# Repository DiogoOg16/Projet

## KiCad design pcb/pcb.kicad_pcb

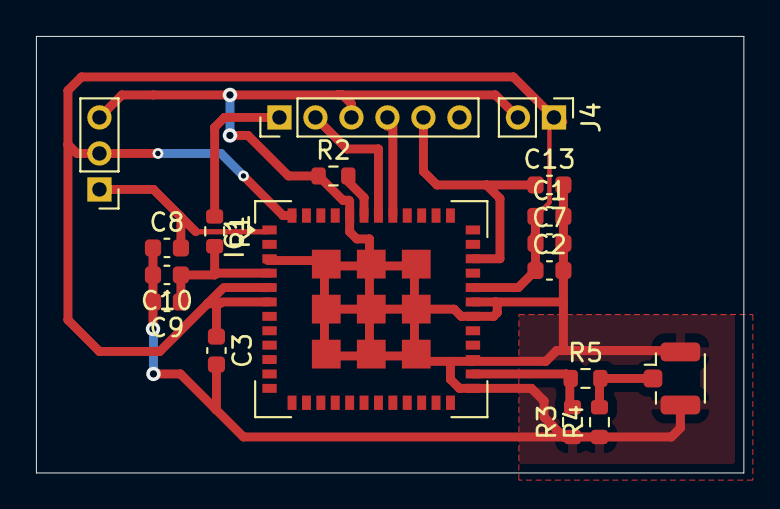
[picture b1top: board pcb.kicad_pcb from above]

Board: 2 copper layers, 39.3 x 24.2 mm, 18 parts (0 on the bottom side), 11 nets.

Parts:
C1, C9: 10uf; C_0603_1608Metric
C2, C13: 1uf; C_0603_1608Metric
C3, C7, C10: 0.1uf; C_0603_1608Metric
C8: 100pf; C_0603_1608Metric
IC1: CMWX1ZZABZ-093; CMWX1ZZABZ
J1: U.FL-R-SMT_01_; U.FL_Hirose_U.FL-R-SMT-1_Vertical
J2: Conn_01x06; PinHeader_1x06_P2.00mm_Vertical
J3: Conn_01x03_Pin; PinHeader_1x03_P2.00mm_Vertical
J4: Conn_01x02_Pin; PinHeader_1x02_P2.00mm_Vertical
R1, R5: 0R; R_0603_1608Metric
R2: 1M; R_0603_1608Metric
R3, R4: DNP; R_0603_1608Metric

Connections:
/debimetre: C8.2, IC1.1 (PA12/USB_DP_), J3.1
/rst: C13.1, IC1.34 (MCU_NRST), J2.5
/swclk: IC1.42 (PA14/SWCLK), J2.2
/swdio: IC1.41 (PA13/SWDIO), J2.4
/vdd: C1.1, C2.1, C3.1, C7.1, IC1.5 (VDD_MCU), IC1.6 (VDD_RF), IC1.32 (VREF+), IC1.48 (VDD__TCXO), J3.2, J4.1
/vdd_usb: C9.1, C10.1, IC1.4 (VDD_USB), R1.2
Earth: C1.2, C2.2, C3.2, C7.2, C8.1, C9.2, C10.2, C13.2, IC1.3 (GND_1), IC1.25 (GND_3), IC1.27 (GND_4), IC1.30 (DBG_CRF2), IC1.31 (STSAFE_NRST), IC1.44 (GND_5), IC1.49 (GND_6), IC1.50 (GND_7), IC1.51 (GND_8), IC1.52 (GND_9), IC1.53 (GND_10), IC1.54 (GND_11), IC1.55 (GND_12), IC1.56 (GND_13), IC1.57 (GND_14), J1.2 (GND), J2.3, J3.3, J4.2, R2.1, R3.1, R4.1
unnamed: IC1.26 (ANT), R3.2, R5.1
unnamed: IC1.43 (BOOT0), R2.2
unnamed: J1.1 (GND), R4.2, R5.2
unnamed: J2.1, R1.1
